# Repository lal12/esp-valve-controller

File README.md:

# ESP32 heating valve controller

This projects is about an ESP32 based heating valve controller using Homematic IP actors to control heating valves,
usually for floorboard heating.

## ESPHOME

Included in this repository are esphome configs for controlling the motors.
Include them with the following lines in your esphome config yml:

```
packages:
  valve_controller_2_0:
    url: https://github.com/lal12/esp-valve-controller
    ref: master
    file: esphome/v2.0.yml
    refresh: 1d # optional
    vars:
      LED_INTERNAL: false
  valve_controller_1_0:
    url: https://github.com/lal12/esp-valve-controller
    ref: master
    file: esphome/v1.0.yml
    refresh: 1d # optional
```

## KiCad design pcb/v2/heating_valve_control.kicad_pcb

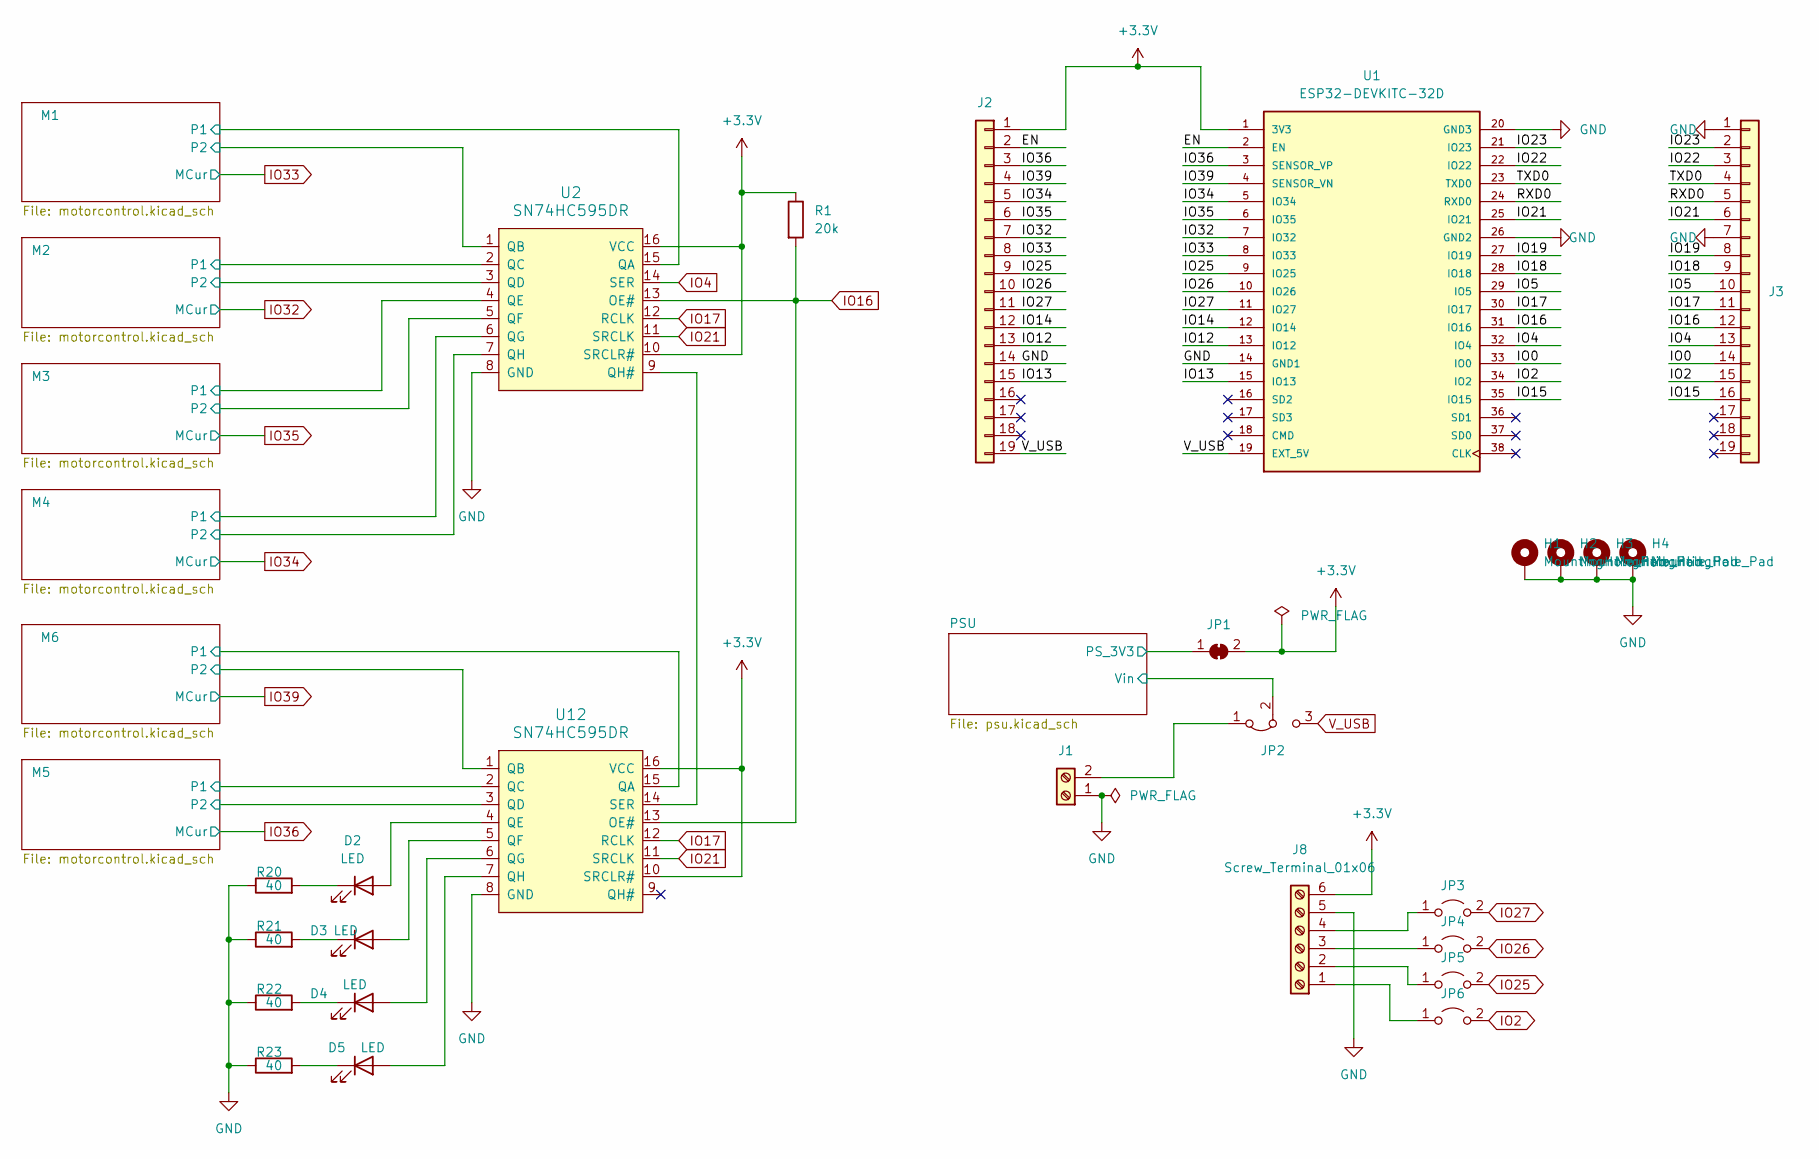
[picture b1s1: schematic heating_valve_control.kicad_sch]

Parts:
D2, D3, D4, D5: LED; LED0603-R-RD_WHITE
H1, H2, H3, H4: MountingHole_Pad; MountingHole_3.2mm_M3_Pad_TopBottom
J1: Screw_Terminal_01x02; TerminalBlock_bornier-2_P5.08mm
J2, J3: Conn_01x19; PinHeader_1x19_P2.54mm_Vertical
J8: Screw_Terminal_01x06; TerminalBlock_RND_205-00236_1x06_P5.08mm_Horizontal
JP1: SolderJumper_2_Bridged; SolderJumper-2_P1.3mm_Bridged_RoundedPad1.0x1.5mm
JP2: Jumper_3_Bridged12; PinHeader_1x03_P2.54mm_Vertical
JP3, JP4, JP5, JP6: Jumper_2_Open; TestPoint_2Pads_Pitch2.54mm_Drill0.8mm
R1: 20k; R_0402_1005Metric_Pad0.72x0.64mm_HandSolder
R20, R21, R22, R23: 40; R_0402_1005Metric_Pad0.72x0.64mm_HandSolder
U1: ESP32-DEVKITC-32D; MODULE_ESP32-DEVKITC-32D; PARTREV 4
U2, U12: SN74HC595DR; SOIC-16_L9.9-W3.9-P1.27-LS6.0-BL; LCSC Part C10092

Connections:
+3.3V: J2.1, J8.6, JP1.2 (B), R1.1, U1.1 (3V3), U2.10 (SRCLR#), U2.16 (VCC), U12.10 (SRCLR#), U12.16 (VCC); also elsewhere on the board
/EN: J2.2, U1.2 (EN)
/IO0: J3.14, U1.33 (IO0)
/IO5: J3.10, U1.29 (IO5)
/IO12: J2.13, U1.13 (IO12)
/IO13: J2.15, U1.15 (IO13)
/IO14: J2.12, U1.12 (IO14)
/IO15: J3.16, U1.35 (IO15)
/IO18: J3.9, U1.28 (IO18)
/IO19: J3.8, U1.27 (IO19)
/IO22: J3.3, U1.22 (IO22)
/IO23: J3.2, U1.21 (IO23)
/M1/P1: U2.15 (QA); also elsewhere on the board
/M1/P2: U2.1 (QB); also elsewhere on the board
/M2/P1: U2.2 (QC); also elsewhere on the board
/M2/P2: U2.3 (QD); also elsewhere on the board
/M3/P1: U2.4 (QE); also elsewhere on the board
/M3/P2: U2.5 (QF); also elsewhere on the board
/M4/P1: U2.6 (QG); also elsewhere on the board
/M4/P2: U2.7 (QH); also elsewhere on the board
/M5/P1: U12.2 (QC); also elsewhere on the board
/M5/P2: U12.3 (QD); also elsewhere on the board
/M6/P1: U12.15 (QA); also elsewhere on the board
/M6/P2: U12.1 (QB); also elsewhere on the board
/PSU/PS_3V3: JP1.1 (A); also elsewhere on the board
/PSU/Vin: JP2.2 (C); also elsewhere on the board
/RXD0: J3.5, U1.24 (RXD0)
/TXD0: J3.4, U1.23 (TXD0)
GND: H1.1, H2.1, H3.1, H4.1, J1.1, J2.14, J3.1, J3.7, J8.5, R20.1, R21.1, R22.1, R23.1, U1.14 (GND1), U1.20 (GND3), U1.26 (GND2), U2.8 (GND), U12.8 (GND); also elsewhere on the board
IO2: J3.15, JP6.2 (B), U1.34 (IO2)
IO4: J3.13, U1.32 (IO4), U2.14 (SER)
IO16: J3.12, R1.2, U1.31 (IO16), U2.13 (OE#), U12.13 (OE#)
IO17: J3.11, U1.30 (IO17), U2.12 (RCLK), U12.12 (RCLK)
IO21: J3.6, U1.25 (IO21), U2.11 (SRCLK), U12.11 (SRCLK)
IO25: J2.9, JP5.2 (B), U1.9 (IO25)
IO26: J2.10, JP4.2 (B), U1.10 (IO26)
IO27: J2.11, JP3.2 (B), U1.11 (IO27)
IO32: J2.7, U1.7 (IO32); also elsewhere on the board
IO33: J2.8, U1.8 (IO33); also elsewhere on the board
IO34: J2.5, U1.5 (IO34); also elsewhere on the board
IO35: J2.6, U1.6 (IO35); also elsewhere on the board
IO36: J2.3, U1.3 (SENSOR_VP); also elsewhere on the board
IO39: J2.4, U1.4 (SENSOR_VN); also elsewhere on the board
unnamed: D2.2 (A), U12.4 (QE)
unnamed: D2.1 (K), R20.2
unnamed: D3.2 (A), U12.5 (QF)
unnamed: D3.1 (K), R21.2
unnamed: D4.2 (A), U12.6 (QG)
unnamed: D4.1 (K), R22.2
unnamed: D5.2 (A), U12.7 (QH)
unnamed: D5.1 (K), R23.2
unnamed: J1.2, JP2.1 (A)
unnamed: J8.1, JP6.1 (A)
unnamed: J8.2, JP5.1 (A)
unnamed: J8.3, JP4.1 (A)
unnamed: J8.4, JP3.1 (A)
unnamed: U2.9 (QH#), U12.14 (SER)
V_USB: J2.19, JP2.3 (B), U1.19 (EXT_5V)

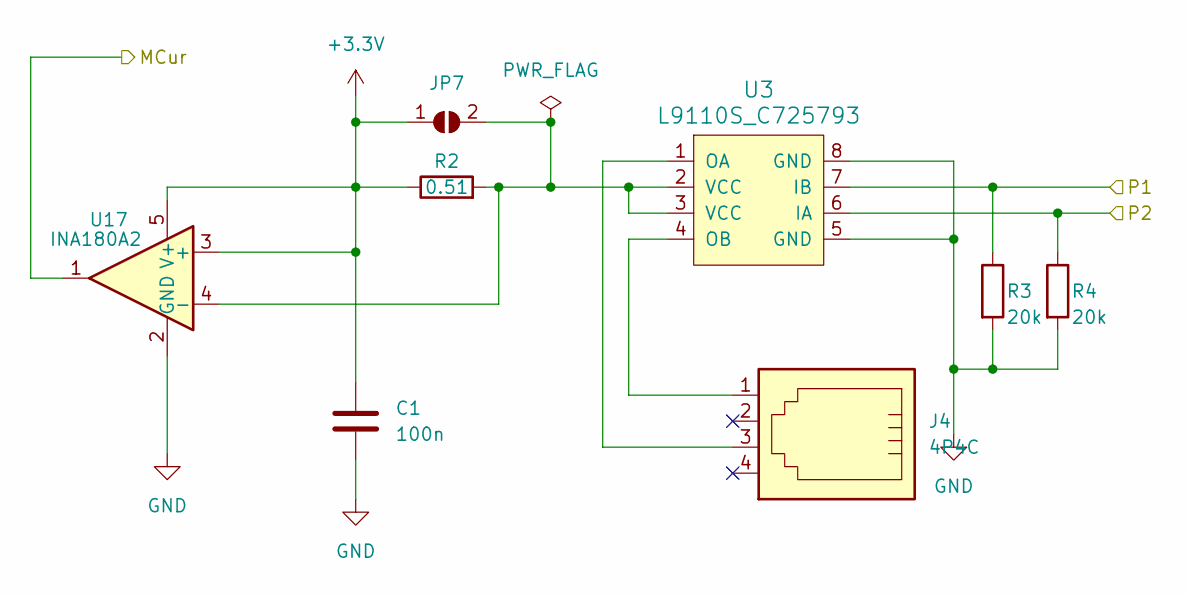
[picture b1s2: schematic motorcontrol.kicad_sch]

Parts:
C1: 100n; C_0603_1608Metric_Pad1.08x0.95mm_HandSolder
J4: 4P4C; RJ11-TH_616-PCB-4P4C-90
JP7: SolderJumper_2_Open; SolderJumper-2_P1.3mm_Open_RoundedPad1.0x1.5mm
R2: 0.51; R_1206_3216Metric_Pad1.30x1.75mm_HandSolder
R3, R4: 20k; R_0402_1005Metric_Pad0.72x0.64mm_HandSolder
U3: L9110S_C725793; SOP-8_L6.1-W3.9-P1.27-LS6.0-BL-1; LCSC Part C725793
U17: INA180A2; SOT-23-5

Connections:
+3.3V: C1.1, JP7.1 (A), R2.1, U17.3 (+), U17.5 (V+); also elsewhere on the board
/M1/P1: R3.1, U3.7 (IB); also elsewhere on the board
/M1/P2: R4.1, U3.6 (IA); also elsewhere on the board
GND: C1.2, R3.2, R4.2, U3.5 (GND), U3.8 (GND), U17.2 (GND); also elsewhere on the board
IO33: U17.1; also elsewhere on the board
unnamed: JP7.2 (B), R2.2, U3.2 (VCC), U3.3 (VCC), U17.4 (-)
unnamed: J4.3, U3.1 (OA)
unnamed: J4.1, U3.4 (OB)

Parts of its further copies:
C2, C3, C4, C7, C8: 100n; C_0603_1608Metric_Pad1.08x0.95mm_HandSolder
J5, J6, J7, J9, J10: 4P4C; RJ11-TH_616-PCB-4P4C-90
JP8, JP9, JP10, JP11, JP12: SolderJumper_2_Open; SolderJumper-2_P1.3mm_Open_RoundedPad1.0x1.5mm
R5, R8, R11, R14, R17: 0.51; R_1206_3216Metric_Pad1.30x1.75mm_HandSolder
R6, R7, R9, R10, R12, R13, R15, R16, R18, R19: 20k; R_0402_1005Metric_Pad0.72x0.64mm_HandSolder
U5, U7, U9, U13, U15: L9110S_C725793; SOP-8_L6.1-W3.9-P1.27-LS6.0-BL-1; LCSC Part C725793
U18, U19, U20, U21, U22: INA180A2; SOT-23-5

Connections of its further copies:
+3.3V: C2.1, C3.1, C4.1, C7.1, C8.1, JP8.1 (A), JP9.1 (A), JP10.1 (A), JP11.1 (A), JP12.1 (A), R5.1, R8.1, R11.1, R14.1, R17.1, U18.3 (+), U18.5 (V+), U19.3 (+), U19.5 (V+), U20.3 (+), U20.5 (V+), U21.3 (+), U21.5 (V+), U22.3 (+), U22.5 (V+); also elsewhere on the board
/M2/P1: R6.1, U5.7 (IB); also elsewhere on the board
/M2/P2: R7.1, U5.6 (IA); also elsewhere on the board
/M3/P1: R9.1, U7.7 (IB); also elsewhere on the board
/M3/P2: R10.1, U7.6 (IA); also elsewhere on the board
/M4/P1: R12.1, U9.7 (IB); also elsewhere on the board
/M4/P2: R13.1, U9.6 (IA); also elsewhere on the board
/M5/P1: R18.1, U15.7 (IB); also elsewhere on the board
/M5/P2: R19.1, U15.6 (IA); also elsewhere on the board
/M6/P1: R15.1, U13.7 (IB); also elsewhere on the board
/M6/P2: R16.1, U13.6 (IA); also elsewhere on the board
GND: C2.2, C3.2, C4.2, C7.2, C8.2, R6.2, R7.2, R9.2, R10.2, R12.2, R13.2, R15.2, R16.2, R18.2, R19.2, U5.5 (GND), U5.8 (GND), U7.5 (GND), U7.8 (GND), U9.5 (GND), U9.8 (GND), U13.5 (GND), U13.8 (GND), U15.5 (GND), U15.8 (GND), U18.2 (GND), U19.2 (GND), U20.2 (GND), U21.2 (GND), U22.2 (GND); also elsewhere on the board
IO32: U18.1; also elsewhere on the board
IO34: U20.1; also elsewhere on the board
IO35: U19.1; also elsewhere on the board
IO36: U22.1; also elsewhere on the board
IO39: U21.1; also elsewhere on the board
unnamed: JP8.2 (B), R5.2, U5.2 (VCC), U5.3 (VCC), U18.4 (-)
unnamed: JP9.2 (B), R8.2, U7.2 (VCC), U7.3 (VCC), U19.4 (-)
unnamed: JP10.2 (B), R11.2, U9.2 (VCC), U9.3 (VCC), U20.4 (-)
unnamed: JP11.2 (B), R14.2, U13.2 (VCC), U13.3 (VCC), U21.4 (-)
unnamed: JP12.2 (B), R17.2, U15.2 (VCC), U15.3 (VCC), U22.4 (-)
unnamed: J5.3, U5.1 (OA)
unnamed: J5.1, U5.4 (OB)
unnamed: J6.3, U7.1 (OA)
unnamed: J6.1, U7.4 (OB)
unnamed: J7.3, U9.1 (OA)
unnamed: J7.1, U9.4 (OB)
unnamed: J9.3, U13.1 (OA)
unnamed: J9.1, U13.4 (OB)
unnamed: J10.3, U15.1 (OA)
unnamed: J10.1, U15.4 (OB)

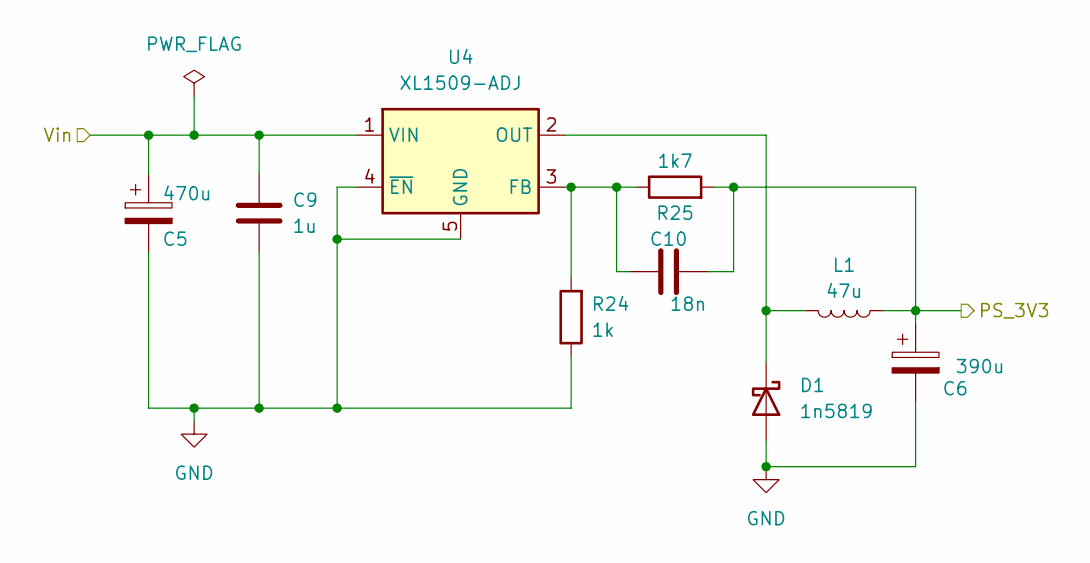
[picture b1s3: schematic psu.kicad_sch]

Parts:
C5: 470u; CAP-SMD_BD10.0-L10.3-W10.3-LS11.3-FD
C6: 390u; CAP-SMD_BD10.0-L10.3-W10.3-LS11.3-FD
C9: 1u; C_0603_1608Metric_Pad1.08x0.95mm_HandSolder
C10: 18n; C_0603_1608Metric_Pad1.08x0.95mm_HandSolder
D1: 1n5819; D_SOD-323_HandSoldering
L1: 47u; IND-SMD_L7.1-W6.6
R24: 1k; R_0402_1005Metric_Pad0.72x0.64mm_HandSolder
R25: 1k7; R_0402_1005Metric_Pad0.72x0.64mm_HandSolder
U4: XL1509-ADJ; SOIC-8_3.9x4.9mm_P1.27mm

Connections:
/PSU/PS_3V3: C6.1, C10.2, L1.1, R25.2; also elsewhere on the board
/PSU/Vin: C5.1, C9.1, U4.1 (VIN); also elsewhere on the board
GND: C5.2, C6.2, C9.2, D1.2 (A), R24.1, U4.4 (~EN), U4.5 (GND), U4.6 (GND), U4.7 (GND), U4.8 (GND); also elsewhere on the board
unnamed: D1.1 (K), L1.2, U4.2 (OUT)
unnamed: C10.1, R24.2, R25.1, U4.3 (FB)

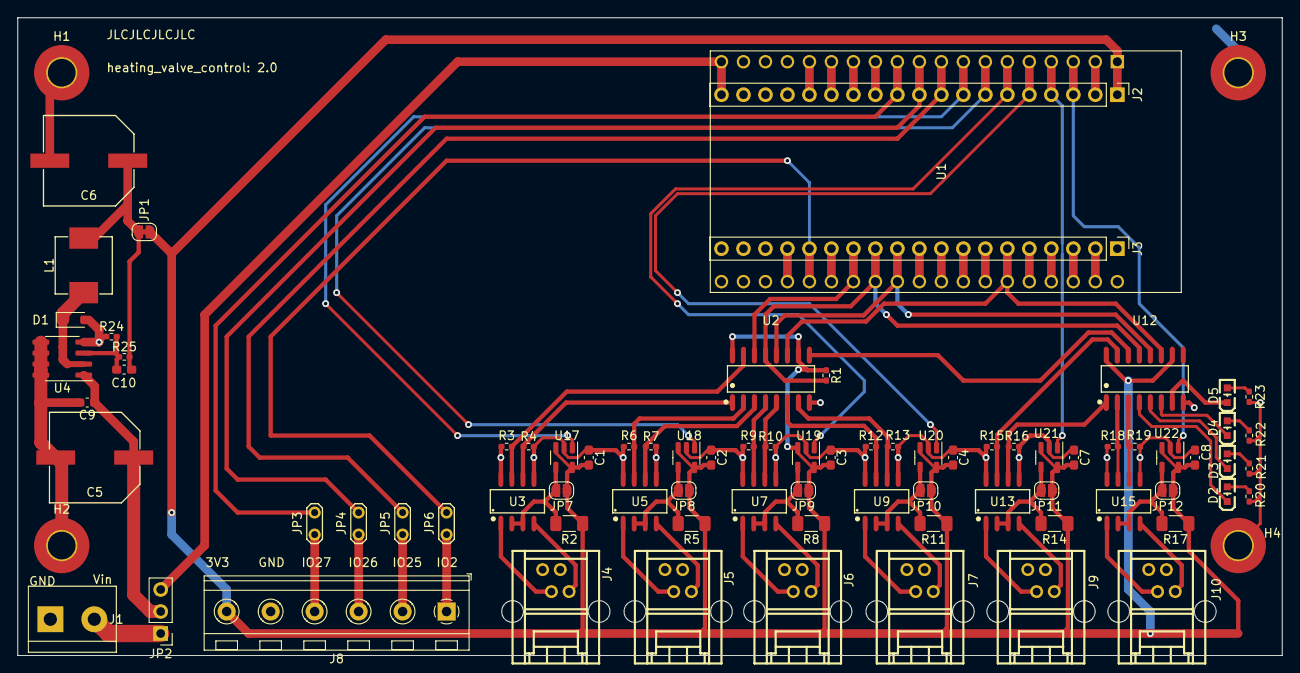
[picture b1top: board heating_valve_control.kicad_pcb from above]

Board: 2 copper layers, 146.1 x 73.7 mm, 83 parts (0 on the bottom side), 78 nets.

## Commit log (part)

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2023-08-20 v2.0: made LED internal configurable
2023-08-20 added v1.0
2023-09-27 - made more variables configurable - removed accidental LED entries for v1
2024-04-23 added case and pcb
2024-12-17 v1.0.yml make CURRENT_THRESHOLD substititutable and slightly increase default
2024-12-17 motor made internals hidden (internal: true)
2024-12-17 increased current threshold
